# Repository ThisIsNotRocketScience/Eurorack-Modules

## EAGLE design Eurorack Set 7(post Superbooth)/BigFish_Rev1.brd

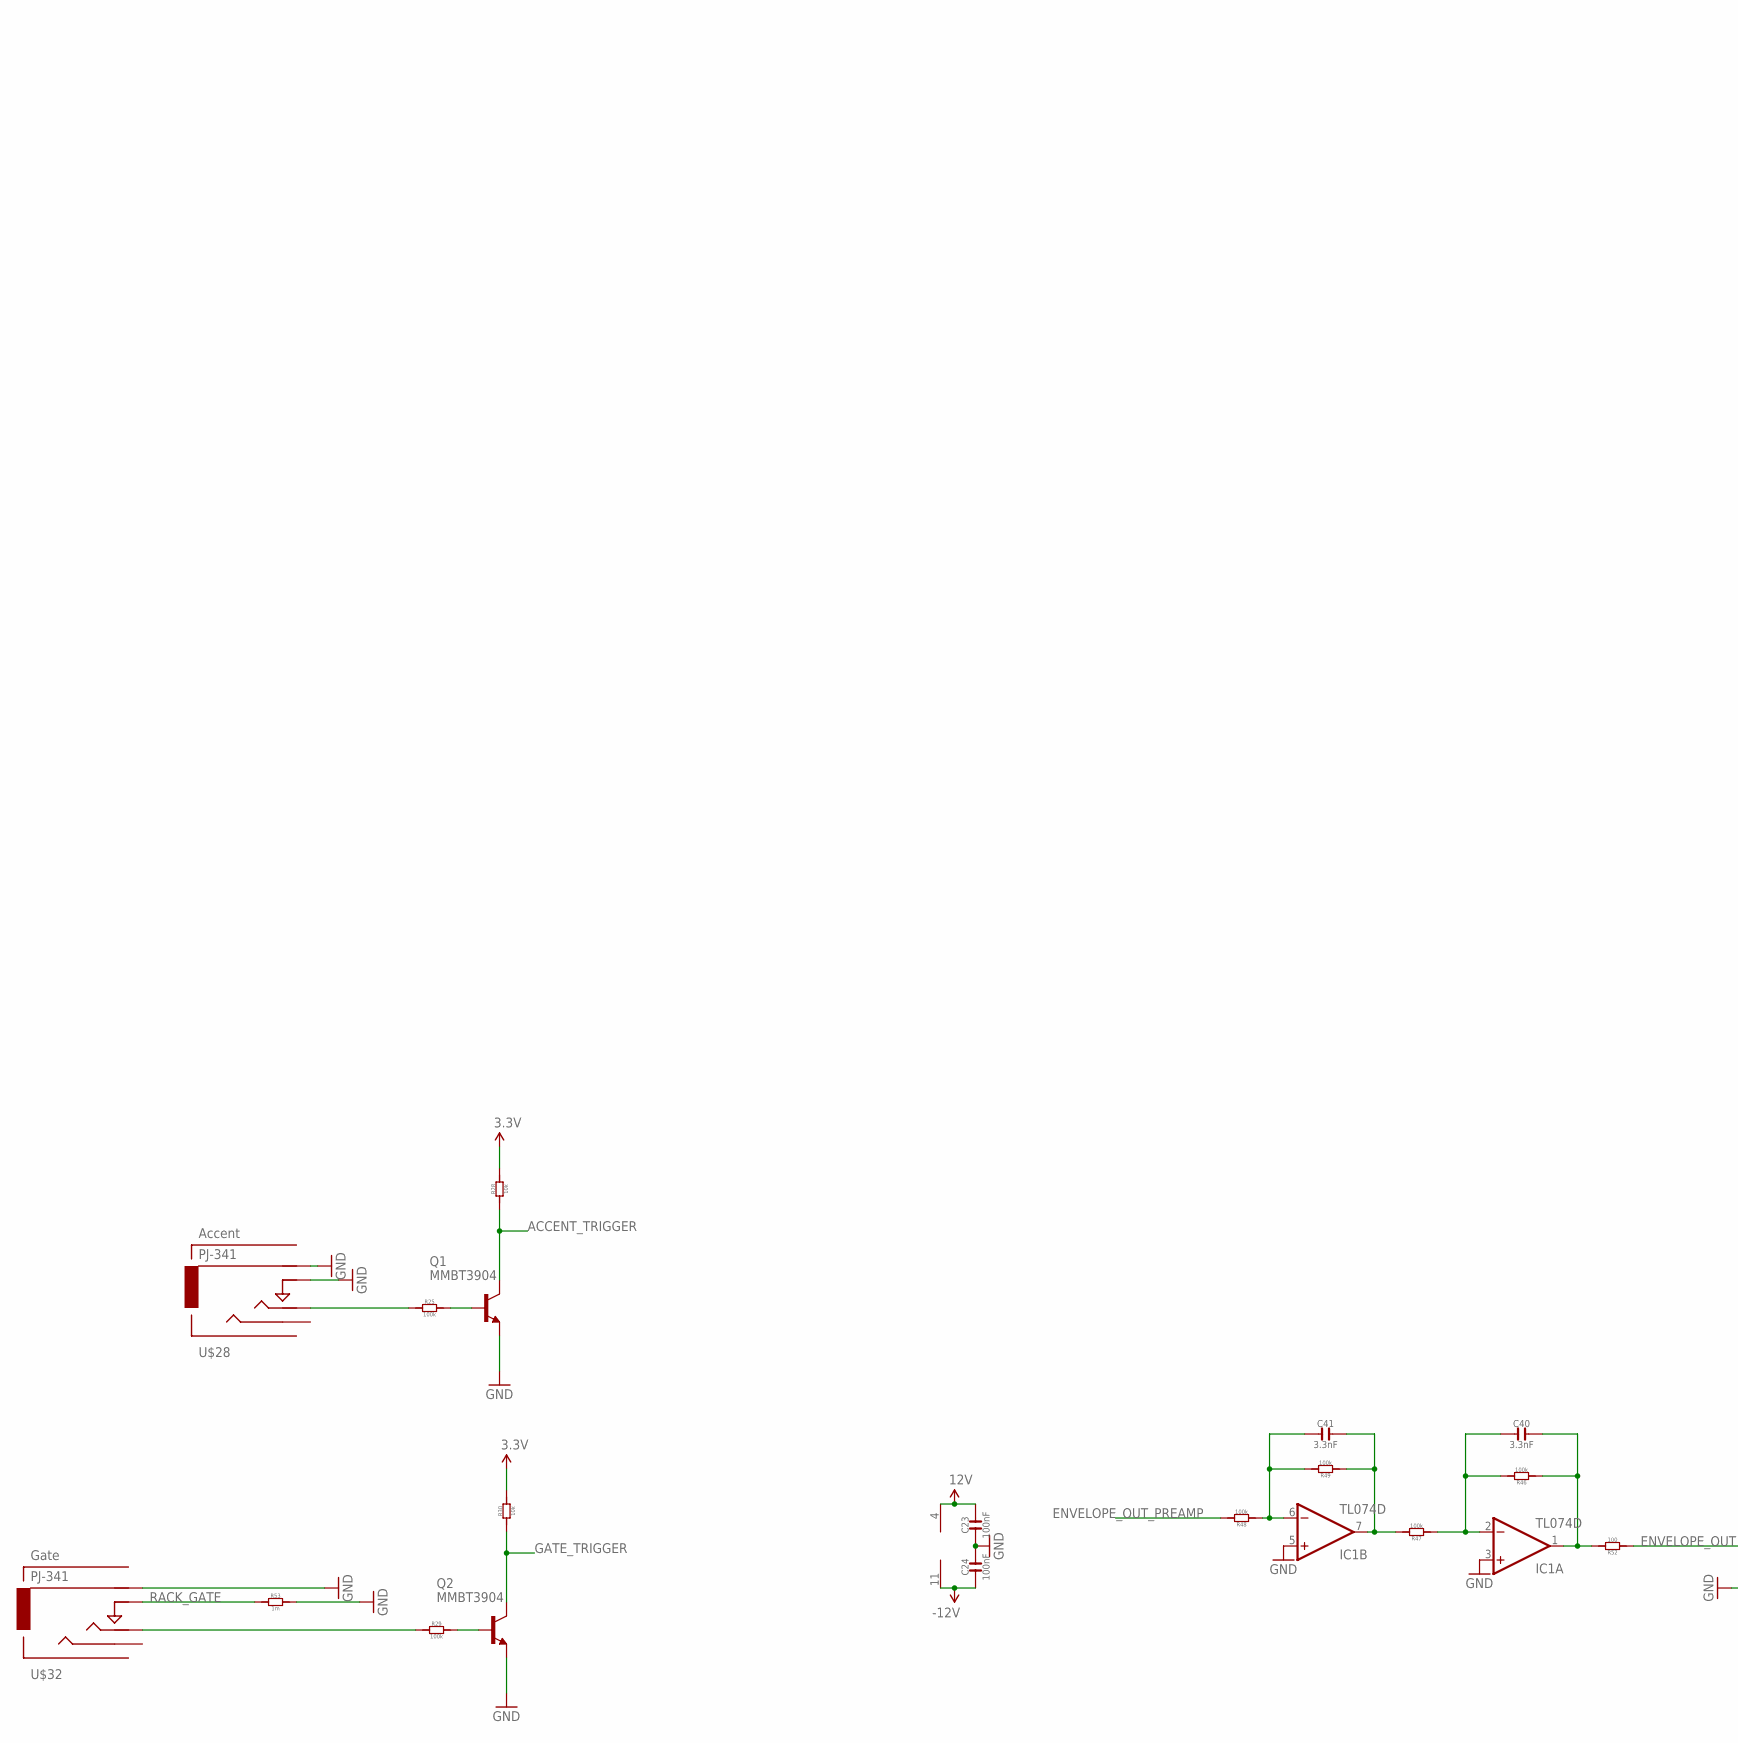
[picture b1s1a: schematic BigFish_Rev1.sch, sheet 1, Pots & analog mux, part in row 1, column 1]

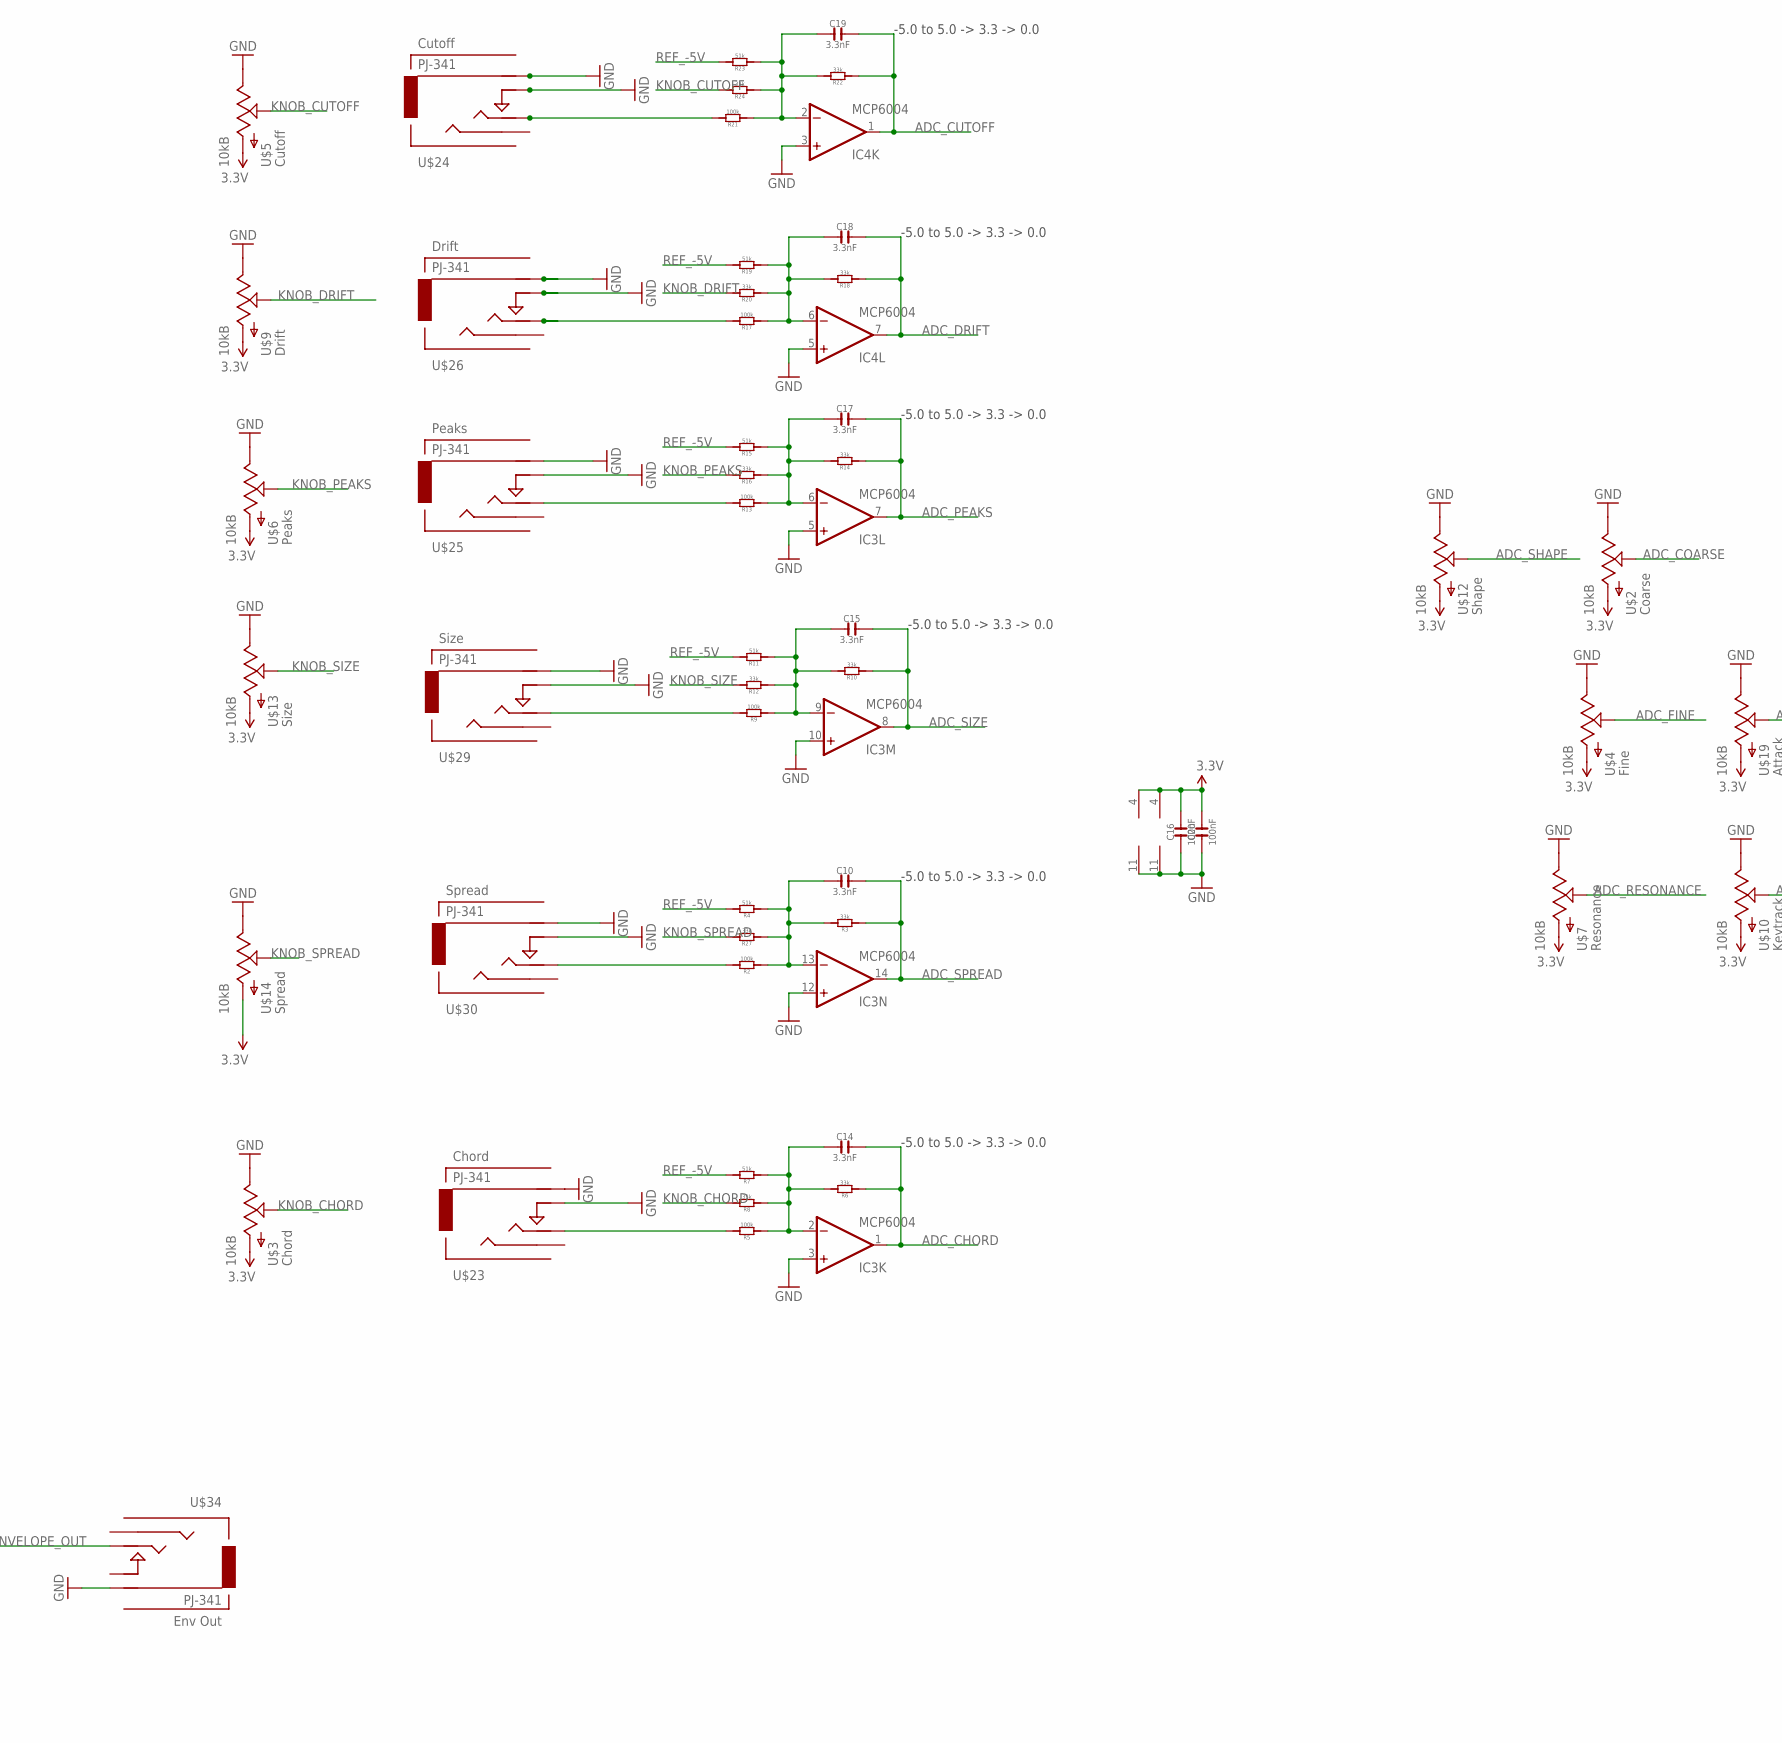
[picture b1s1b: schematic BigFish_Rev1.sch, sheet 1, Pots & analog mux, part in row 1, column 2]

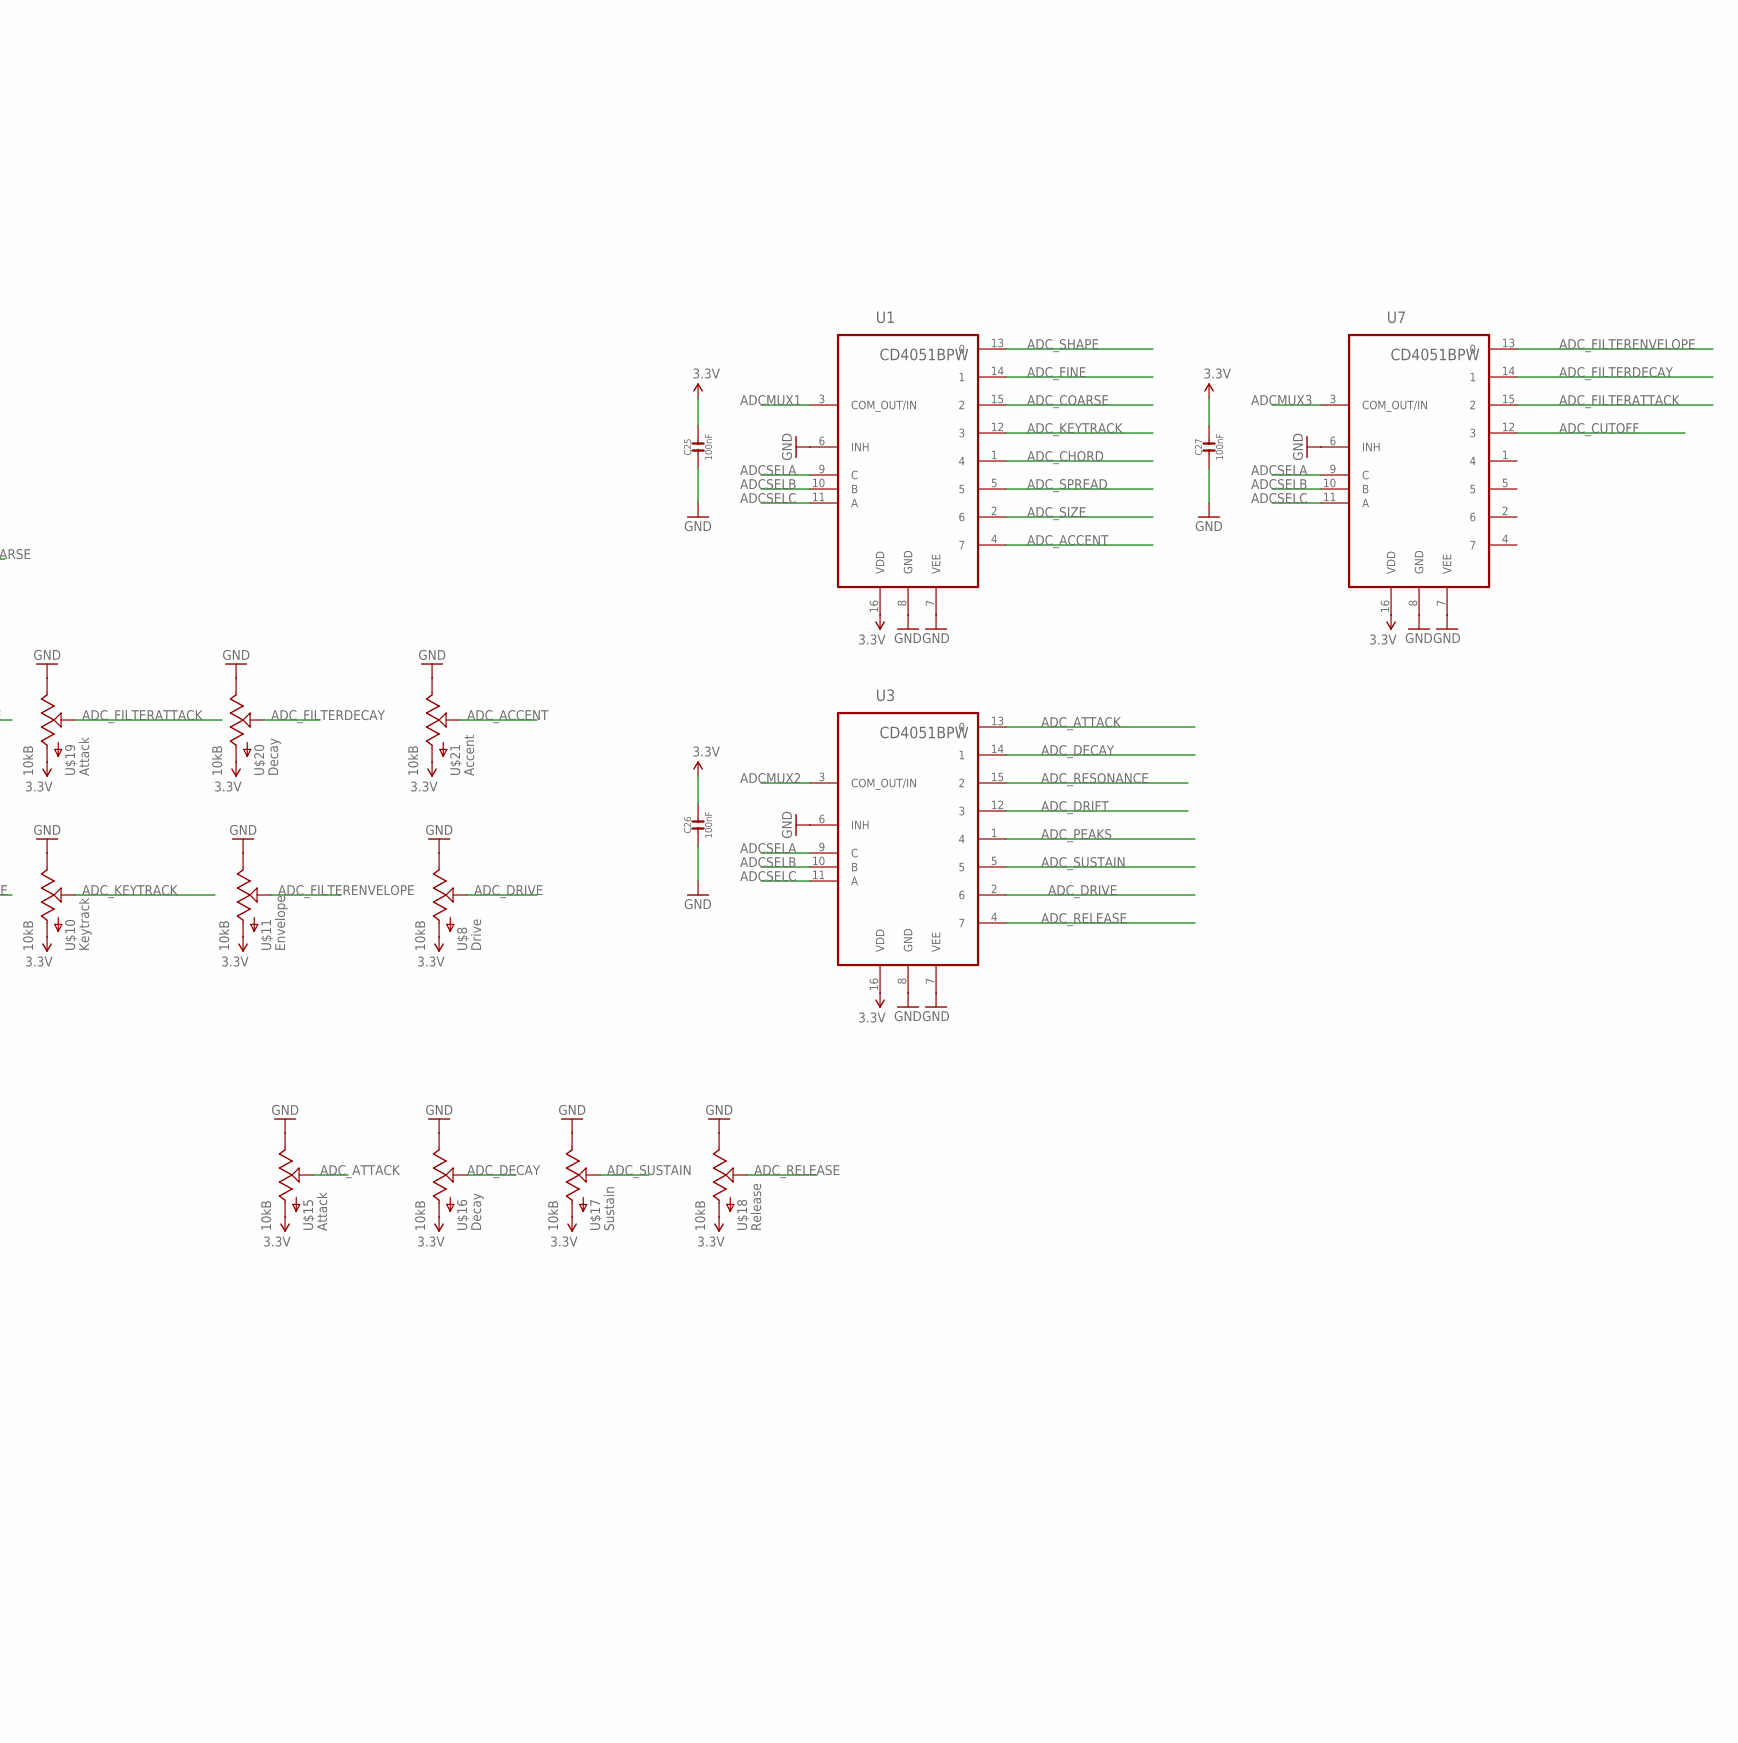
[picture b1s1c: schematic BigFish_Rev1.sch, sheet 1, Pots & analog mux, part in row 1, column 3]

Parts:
C10, C14, C15, C17, C18, C19, C40, C41: 3.3nF; C0603
C16, C20, C23, C24, C25, C26, C27: 100nF; C0603
IC1: TL074D; SO14
IC3, IC4: MCP6004; SO14; MPN MCP6004-I/SL.
Q1, Q2: MMBT3904; SOT23-BEC; MPN PMBT3904,215
R2, R5, R9, R13, R17, R21, R25, R29, R46, R47, R48, R49: 100k; R0603
R3, R6, R8, R10, R12, R14, R16, R18, R20, R22, R24, R27: 33k; R0603
R4, R7, R11, R15, R19, R23: 51k; R0603
R28, R30: 10k; R0603
R52: 100; R0603
R53: 1m; R0603
U1, U3, U7: CD4051BPW; SOP65P640X120-16N
U$2, U$3, U$4, U$5, U$6, U$7, U$8, U$9, U$10, U$11, U$12, U$13, U$14, U$15, U$16, U$17, U$18, U$19, U$20, U$21: 10kB; OG-POTS_ALPS_POT_VERTICAL
U$23, U$24, U$25, U$26, U$28, U$29, U$30, U$32: PJ-341; 3.5MM-JACK-SWITCH-13MM-INPUT
U$34: PJ-341; 3.5MM-JACK-SWITCH-13MM-OUTPUT

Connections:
3.3V: C16.2, C20.2, C25.2, C26.2, C27.2, IC3.4 (V+), IC4.4 (V+), R28.2, R30.2, U1.16 (VDD), U3.16 (VDD), U7.16 (VDD), U$2.P$3 (A), U$3.P$3 (A), U$4.P$3 (A), U$5.P$3 (A), U$6.P$3 (A), U$7.P$3 (A), U$8.P$3 (A), U$9.P$3 (A), U$10.P$3 (A), U$11.P$3 (A), U$12.P$3 (A), U$13.P$3 (A), U$14.P$3 (A), U$15.P$3 (A), U$16.P$3 (A), U$17.P$3 (A), U$18.P$3 (A), U$19.P$3 (A), U$20.P$3 (A), U$21.P$3 (A); also elsewhere on the board
12V: C23.2, IC1.4 (V+); also elsewhere on the board
-12V: C24.1, IC1.11 (V-); also elsewhere on the board
ACCENT_TRIGGER: Q1.C, R28.1; also elsewhere on the board
ADCMUX1: U1.3 (COM_OUT/IN); also elsewhere on the board
ADCMUX2: U3.3 (COM_OUT/IN); also elsewhere on the board
ADCMUX3: U7.3 (COM_OUT/IN); also elsewhere on the board
ADCSELA: U1.9 (C), U3.9 (C), U7.9 (C); also elsewhere on the board
ADCSELB: U1.10 (B), U3.10 (B), U7.10 (B); also elsewhere on the board
ADCSELC: U1.11 (A), U3.11 (A), U7.11 (A); also elsewhere on the board
ADC_ACCENT: U1.4 (7), U$21.P$2 (S)
ADC_ATTACK: U3.13 (0), U$15.P$2 (S)
ADC_CHORD: C14.2, IC3.1 (OUT), R6.1, U1.1 (4)
ADC_COARSE: U1.15 (2), U$2.P$2 (S)
ADC_CUTOFF: C19.2, IC4.1 (OUT), R22.1, U7.12 (3)
ADC_DECAY: U3.14 (1), U$16.P$2 (S)
ADC_DRIFT: C18.2, IC4.7 (OUT), R18.1, U3.12 (3)
ADC_DRIVE: U3.2 (6), U$8.P$2 (S)
ADC_FILTERATTACK: U7.15 (2), U$19.P$2 (S)
ADC_FILTERDECAY: U7.14 (1), U$20.P$2 (S)
ADC_FILTERENVELOPE: U7.13 (0), U$11.P$2 (S)
ADC_FINE: U1.14 (1), U$4.P$2 (S)
ADC_KEYTRACK: U1.12 (3), U$10.P$2 (S)
ADC_PEAKS: C17.2, IC3.7 (OUT), R14.1, U3.1 (4)
ADC_RELEASE: U3.4 (7), U$18.P$2 (S)
ADC_RESONANCE: U3.15 (2), U$7.P$2 (S)
ADC_SHAPE: U1.13 (0), U$12.P$2 (S)
ADC_SIZE: C15.2, IC3.8 (OUT), R10.1, U1.2 (6)
ADC_SPREAD: C10.2, IC3.14 (OUT), R3.1, U1.5
ADC_SUSTAIN: U3.5, U$17.P$2 (S)
ENVELOPE_OUT: R52.1, U$34.TIP@3 (TIP)
ENVELOPE_OUT_PREAMP: R48.2; also elsewhere on the board
GATE_TRIGGER: Q2.C, R30.1; also elsewhere on the board
GND: C16.1, C20.1, C23.1, C24.2, C25.1, C26.1, C27.1, IC1.3 (+IN), IC1.5 (+IN), IC3.3 (+IN), IC3.5 (+IN), IC3.10 (+IN), IC3.11 (V-), IC3.12 (+IN), IC4.3 (+IN), IC4.5 (+IN), IC4.11 (V-), Q1.E, Q2.E, R53.2, U1.6 (INH), U1.7 (VEE), U1.8 (GND), U3.6 (INH), U3.7 (VEE), U3.8 (GND), U7.6 (INH), U7.7 (VEE), U7.8 (GND), U$2.P$1 (E), U$3.P$1 (E), U$4.P$1 (E), U$5.P$1 (E), U$6.P$1 (E), U$7.P$1 (E), U$8.P$1 (E), U$9.P$1 (E), U$10.P$1 (E), U$11.P$1 (E), U$12.P$1 (E), U$13.P$1 (E), U$14.P$1 (E), U$15.P$1 (E), U$16.P$1 (E), U$17.P$1 (E), U$18.P$1 (E), U$19.P$1 (E), U$20.P$1 (E), U$21.P$1 (E), U$23.RING@3 (RING), U$23.SWITCH@3 (SWITCH), U$24.RING@3 (RING), U$24.SWITCH@3 (SWITCH), U$25.RING@3 (RING), U$25.SWITCH@3 (SWITCH), U$26.RING@3 (RING), U$26.SWITCH@3 (SWITCH), U$28.RING@3 (RING), U$28.SWITCH@3 (SWITCH), U$29.RING@3 (RING), U$29.SWITCH@3 (SWITCH), U$30.RING@3 (RING), U$30.SWITCH@3 (SWITCH), U$32.RING@3 (RING), U$34.RING@3 (RING); also elsewhere on the board
KNOB_CHORD: R8.2, U$3.P$2 (S)
KNOB_CUTOFF: R24.2, U$5.P$2 (S)
KNOB_DRIFT: R20.2, U$9.P$2 (S)
KNOB_PEAKS: R16.2, U$6.P$2 (S)
KNOB_SIZE: R12.2, U$13.P$2 (S)
KNOB_SPREAD: R27.2, U$14.P$2 (S)
unnamed: R17.2, U$26.TIP@3 (TIP)
unnamed: C18.1, IC4.6 (-IN), R17.1, R18.2, R19.1, R20.1
unnamed: R21.2, U$24.TIP@3 (TIP)
unnamed: R2.2, U$30.TIP@3 (TIP)
unnamed: C19.1, IC4.2 (-IN), R21.1, R22.2, R23.1, R24.1
unnamed: C10.1, IC3.13 (-IN), R2.1, R3.2, R4.1, R27.1
unnamed: Q1.B, R25.2
unnamed: R25.1, U$28.TIP@3 (TIP)
unnamed: Q2.B, R29.2
unnamed: R5.2, U$23.TIP@3 (TIP)
unnamed: C14.1, IC3.2 (-IN), R5.1, R6.2, R7.1, R8.1
unnamed: R9.2, U$29.TIP@3 (TIP)
unnamed: C15.1, IC3.9 (-IN), R9.1, R10.2, R11.1, R12.1
unnamed: R13.2, U$25.TIP@3 (TIP)
unnamed: C17.1, IC3.6 (-IN), R13.1, R14.2, R15.1, R16.1
unnamed: R29.1, U$32.TIP@3 (TIP)
unnamed: C40.2, IC1.1 (OUT), R46.1, R52.2
unnamed: C41.1, IC1.6 (-IN), R48.1, R49.2
unnamed: C41.2, IC1.7 (OUT), R47.2, R49.1
unnamed: C40.1, IC1.2 (-IN), R46.2, R47.1
RACK_GATE: R53.1, U$32.SWITCH@3 (SWITCH); also elsewhere on the board
REF_-5V: R4.2, R7.2, R11.2, R15.2, R19.2, R23.2; also elsewhere on the board

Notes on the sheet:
-5.0 to 5.0 -> 3.3 -> 0.0

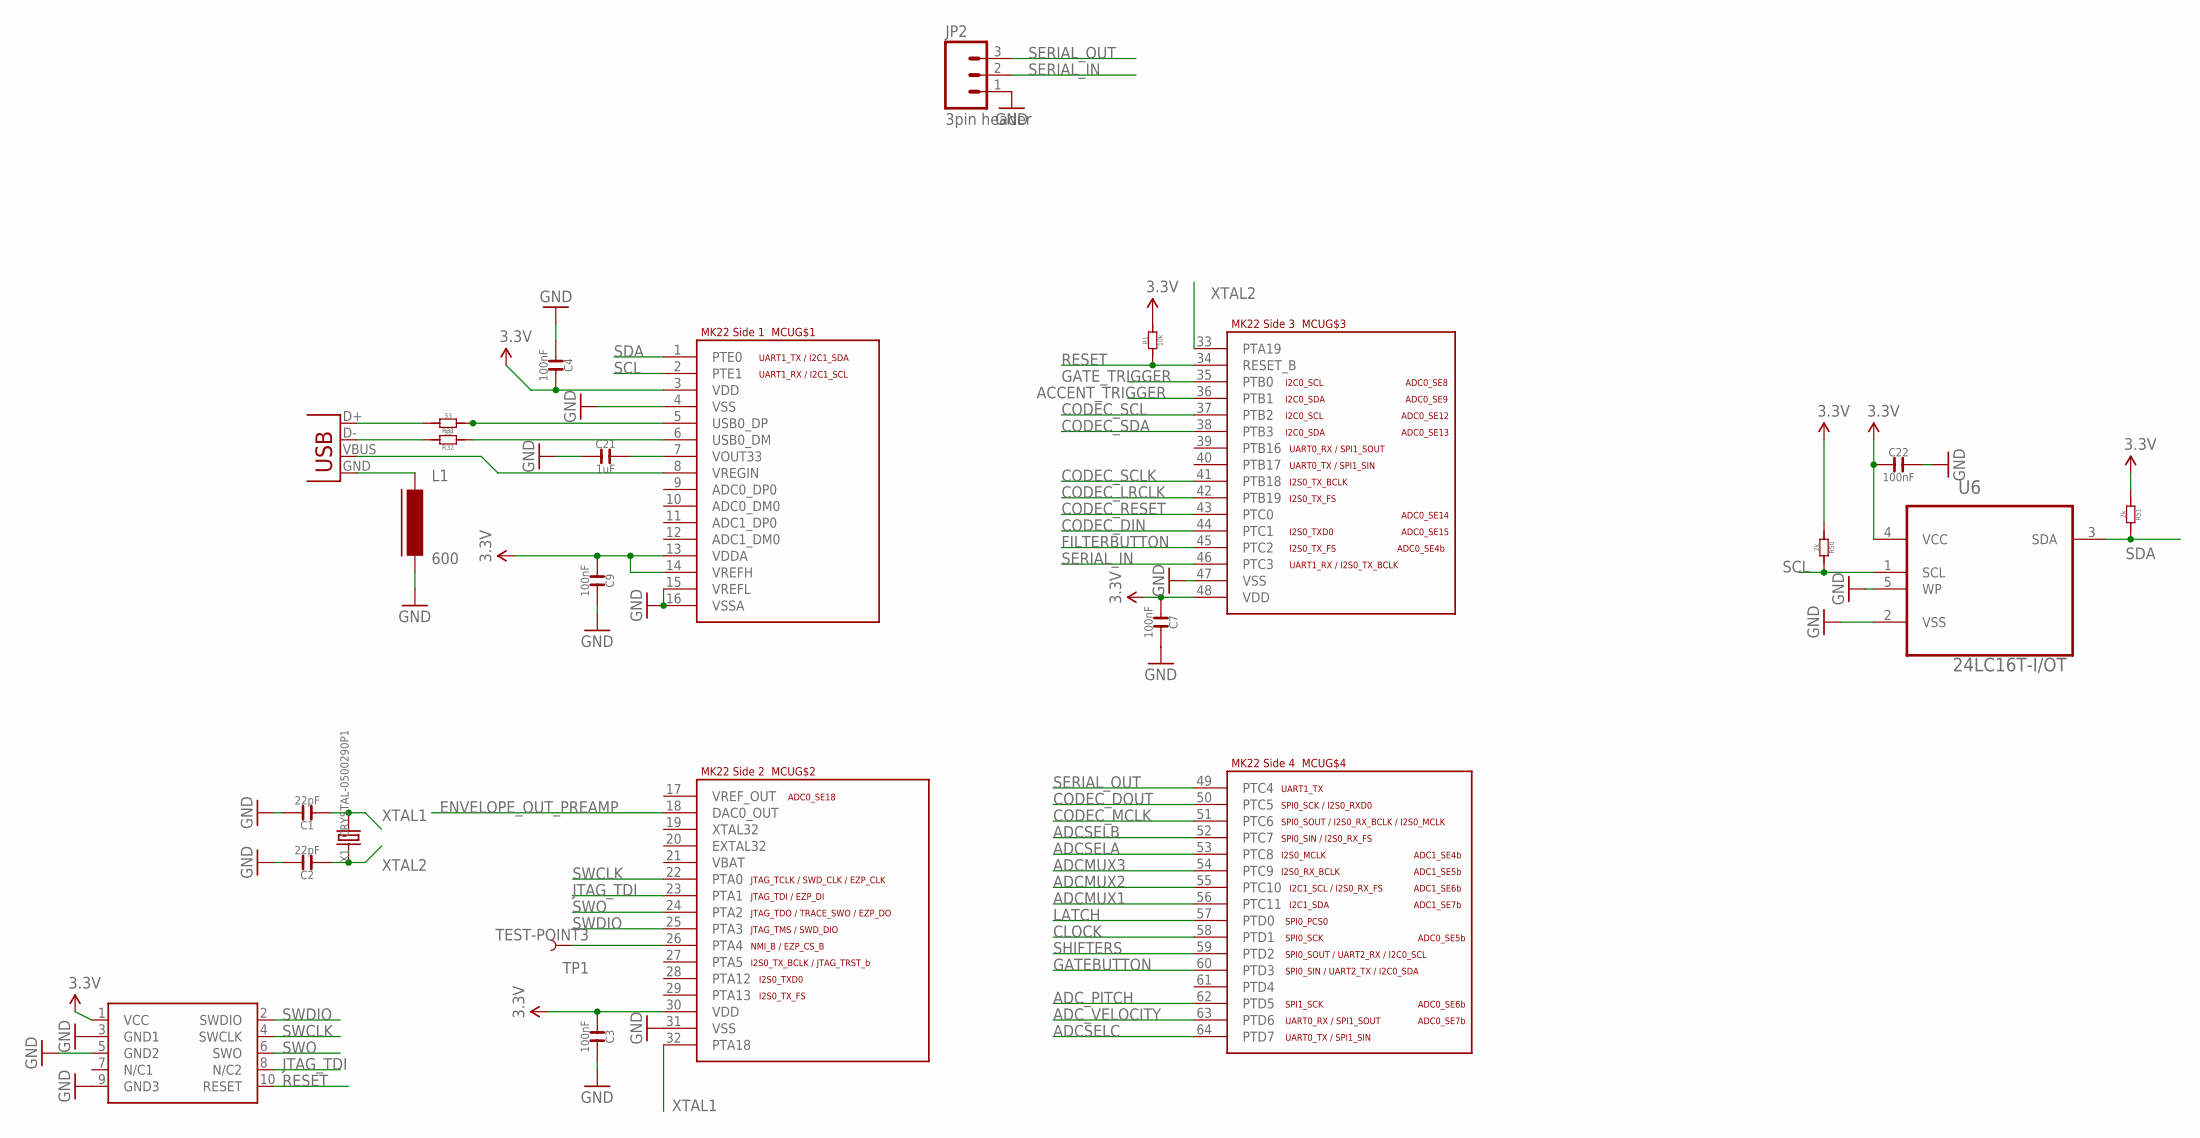
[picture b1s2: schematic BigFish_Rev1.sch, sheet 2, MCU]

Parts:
C1, C2: 22pF; C0603
C3, C4, C7, C9, C22: 100nF; C0603
C21: 1uF; C0603
JP1: USBPTH-VERTICAL; USB-B-PTH-VERTICAL
JP2: 3pin header; 1X03
L1: 600; FB603
MCU: MK22_120_TQFP64; MK22_TQFP64
R1: 10k; R0603
R31, R32: 33; R0603
R50, R51: 2k; R0603
SWD1: CORTEX_SWD; M50-3600542
TP1: TEST-POINT3; PAD.03X.03
U6: 24LC16T-I/OT; SOT95P290X145-5N; MPN 24LC00T-I/OT
X1: CRYSTAL-0500290P1; 2P-SMD-5.0X3.2

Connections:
3.3V: C3.1, C4.2, C7.1, C9.1, C22.1, MCU.3 (VDD), MCU.13 (VDDA), MCU.14 (VREFH), MCU.30 (VDD), MCU.48 (VDD), R1.2, R50.1, R51.1, SWD1.1 (VCC), U6.4 (VCC); also elsewhere on the board
ACCENT_TRIGGER: MCU.36 (PTB1); also elsewhere on the board
ADCMUX1: MCU.56 (PTC11); also elsewhere on the board
ADCMUX2: MCU.55 (PTC10); also elsewhere on the board
ADCMUX3: MCU.54 (PTC9); also elsewhere on the board
ADCSELA: MCU.53 (PTC8); also elsewhere on the board
ADCSELB: MCU.52 (PTC7); also elsewhere on the board
ADCSELC: MCU.64 (PTD7); also elsewhere on the board
ADC_PITCH: MCU.62 (PTD5); also elsewhere on the board
ADC_VELOCITY: MCU.63 (PTD6); also elsewhere on the board
CLOCK: MCU.58 (PTD1); also elsewhere on the board
CODEC_DIN: MCU.44 (PTC1); also elsewhere on the board
CODEC_DOUT: MCU.50 (PTC5); also elsewhere on the board
CODEC_LRCLK: MCU.42 (PTB19); also elsewhere on the board
CODEC_MCLK: MCU.51 (PTC6); also elsewhere on the board
CODEC_RESET: MCU.43 (PTC0); also elsewhere on the board
CODEC_SCL: MCU.37 (PTB2); also elsewhere on the board
CODEC_SCLK: MCU.41 (PTB18); also elsewhere on the board
CODEC_SDA: MCU.38 (PTB3); also elsewhere on the board
ENVELOPE_OUT_PREAMP: MCU.18 (DAC0_OUT); also elsewhere on the board
FILTERBUTTON: MCU.45 (PTC2); also elsewhere on the board
GATEBUTTON: MCU.60 (PTD3); also elsewhere on the board
GATE_TRIGGER: MCU.35 (PTB0); also elsewhere on the board
GND: C1.2, C2.2, C3.2, C4.1, C7.2, C9.2, C21.1, C22.2, JP2.1, L1.2, MCU.4 (VSS), MCU.15 (VREFL), MCU.16 (VSSA), MCU.31 (VSS), MCU.47 (VSS), SWD1.3 (GND1), SWD1.5 (GND2), SWD1.9 (GND3), U6.2 (VSS), U6.5 (WP); also elsewhere on the board
JTAG_TDI: MCU.23 (PTA1), SWD1.8 (N/C2)
LATCH: MCU.57 (PTD0); also elsewhere on the board
unnamed: C21.2, MCU.7 (VOUT33)
unnamed: JP1.D+, R31.2
unnamed: JP1.D-, R32.2
unnamed: JP1.VBUS, MCU.8 (VREGIN)
unnamed: MCU.5 (USB0_DP), R31.1
unnamed: MCU.6 (USB0_DM), R32.1
unnamed: JP1.GND, L1.1
unnamed: MCU.26 (PTA4), TP1.P$1
RESET: MCU.34 (RESET_B), R1.1, SWD1.10 (RESET)
SCL: MCU.2 (PTE1), R50.2, U6.1 (SCL)
SDA: MCU.1 (PTE0), R51.2, U6.3 (SDA)
SERIAL_IN: JP2.2, MCU.46 (PTC3)
SERIAL_OUT: JP2.3, MCU.49 (PTC4)
SHIFTERS: MCU.59 (PTD2); also elsewhere on the board
SWCLK: MCU.22 (PTA0), SWD1.4 (SWCLK)
SWDIO: MCU.25 (PTA3), SWD1.2 (SWDIO)
SWO: MCU.24 (PTA2), SWD1.6 (SWO)
XTAL1: C1.1, MCU.32 (PTA18), X1.2
XTAL2: C2.1, MCU.33 (PTA19), X1.1

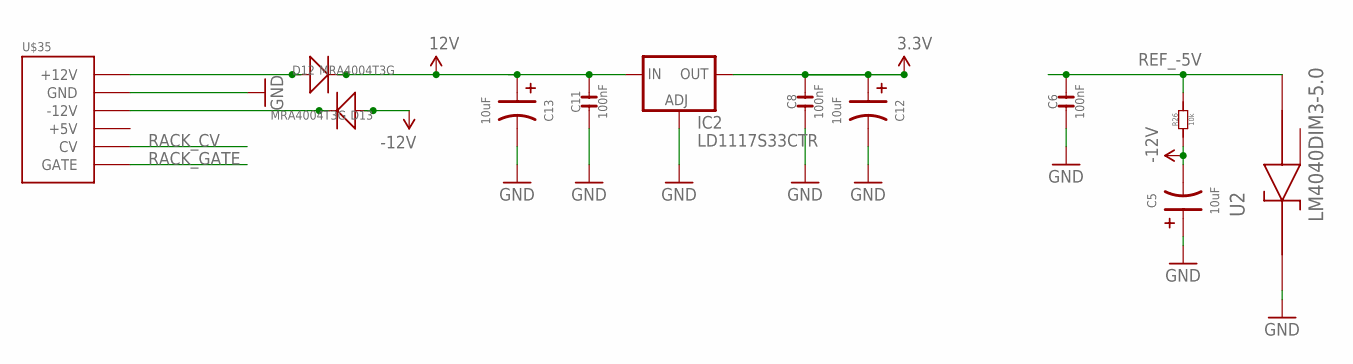
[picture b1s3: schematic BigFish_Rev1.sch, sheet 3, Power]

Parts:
C5, C12, C13: 10uF; AVX-A; MPN TAJB106K020RNJ
C6: 100nF; C0603; MPN 06035C104KAT2A
C8, C11: 100nF; C0603; MPN MC0603F104Z160CT
D12, D13: MRA4004T3G; DO-214AC; MPN US1G-E3/5AT
IC2: LD1117S33CTR; SOT223; MPN LD1117AS33TR
R26: 10k; R0603
U2: LM4040DIM3-5.0; SOT95P237X112-3N
U$35: POWERSMT; 2X08_SMT_HEADER

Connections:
3.3V: C8.2, C12.+ (1), IC2.2 (OUT), IC2.4 (OUT); also elsewhere on the board
12V: C11.2, C13.+ (1), D12.2 (-), IC2.3 (IN); also elsewhere on the board
-12V: C5.- (2), D13.1 (+), R26.1; also elsewhere on the board
GND: C5.+ (1), C6.1, C8.1, C11.1, C12.- (2), C13.- (2), IC2.1 (ADJ), U2.1 (CATHODE), U$35.3 (GND), U$35.4 (GND), U$35.5 (GND), U$35.6 (GND), U$35.7 (GND), U$35.8 (GND); also elsewhere on the board
unnamed: D12.1 (+), U$35.9 (+12V), U$35.10 (+12V)
unnamed: D13.2 (-), U$35.1 (-12V), U$35.2 (-12V)
RACK_CV: U$35.13 (CV), U$35.14 (CV); also elsewhere on the board
RACK_GATE: U$35.15 (GATE), U$35.16 (GATE); also elsewhere on the board
REF_-5V: C6.2, R26.2, U2.2 (ANODE); also elsewhere on the board

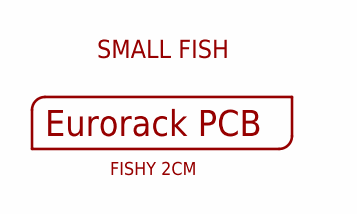
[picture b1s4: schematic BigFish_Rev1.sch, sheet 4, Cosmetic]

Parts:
U$1: EURORACK_PCB24HP; EURORACK24HPPCB
U$45: FISH2CM; FISH
U$49: FISH_SMALL

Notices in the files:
parts and their libraries:
SparkFun-Connectors: Licensing: CC v3.0 Share-Alike You are welcome to use this library for commercial purposes.
